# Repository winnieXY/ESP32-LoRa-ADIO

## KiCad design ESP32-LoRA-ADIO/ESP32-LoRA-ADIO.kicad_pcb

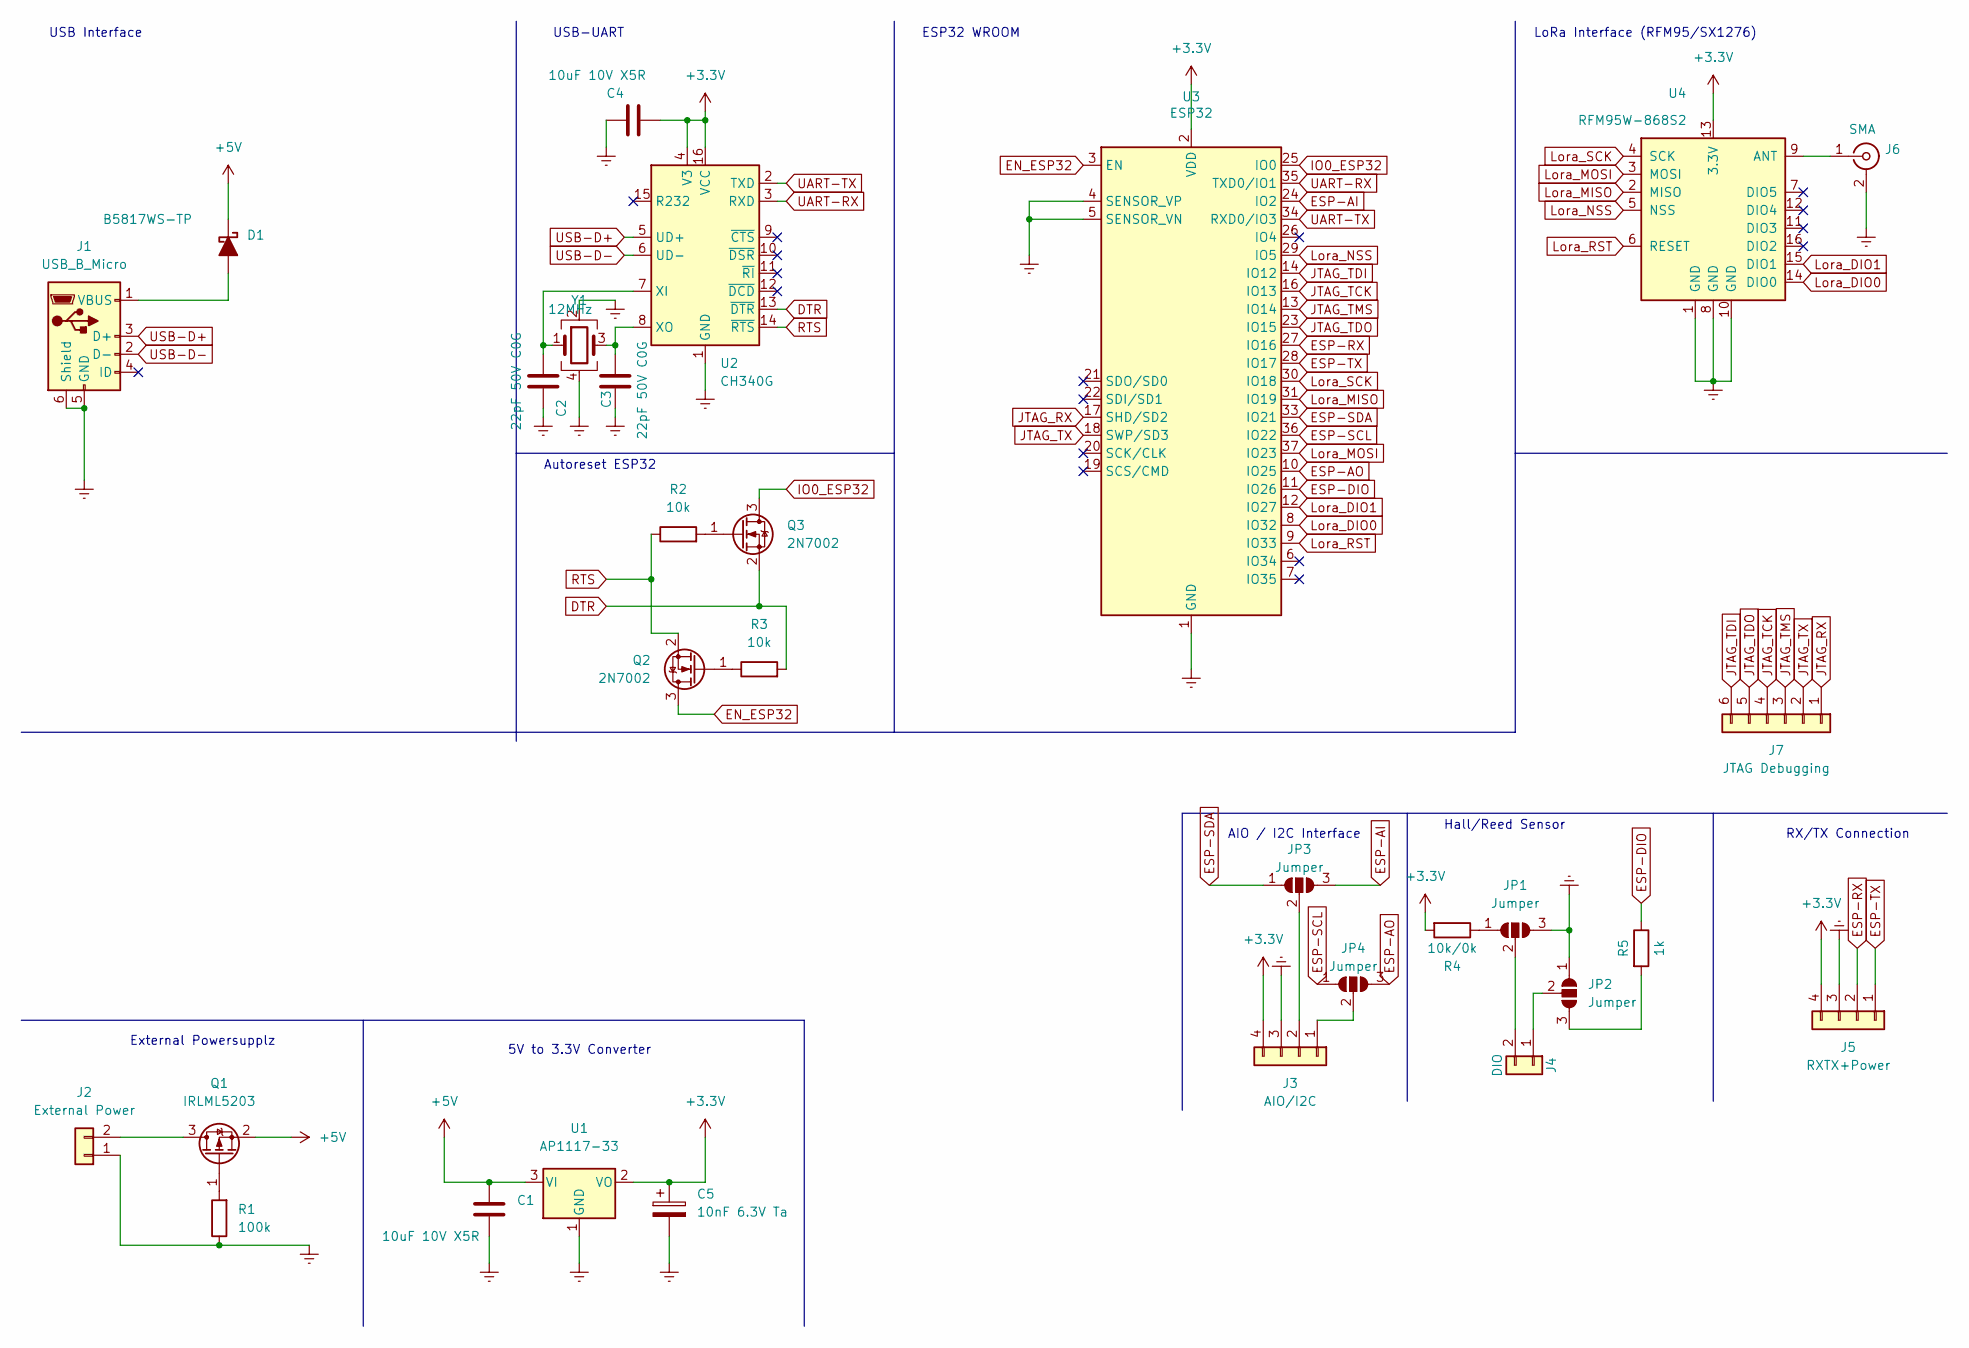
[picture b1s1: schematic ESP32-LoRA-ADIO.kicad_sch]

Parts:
C1, C4: 10uF 10V X5R; C_0603_1608Metric_Pad1.08x0.95mm_HandSolder; LCSC-Part C19702
C2, C3: 22pF 50V C0G; C_0603_1608Metric_Pad1.08x0.95mm_HandSolder; LCSC-Part C1653
C5: 10nF 6.3V Ta; CP_EIA-3528-15_AVX-H_Pad1.50x2.35mm_HandSolder; LCSC-Part C16133
D1: B5817WS-TP; D_SOD-323_HandSoldering; LCSC-Part C123899
J1: USB_B_Micro; GCT_USB3140-30-0230-1-C_REVE1
J2: External Power; JST_XH_B2B-XH-A_1x02_P2.50mm_Vertical
J3: AIO/I2C; JST_XH_B4B-XH-A_1x04_P2.50mm_Vertical
J4: DIO; JST_XH_B2B-XH-A_1x02_P2.50mm_Vertical
J5: RXTX+Power; JST_XH_B4B-XH-A_1x04_P2.50mm_Vertical
J6: SMA; SMA_Amphenol_901-144_Vertical
J7: JTAG Debugging; JST_XH_B6B-XH-A_1x06_P2.50mm_Vertical
JP1, JP2, JP3, JP4: Jumper; SolderJumper-3_P1.3mm_Open_Pad1.0x1.5mm
Q1: IRLML5203; SOT-23; LCSC-Part C2985623
Q2, Q3: 2N7002; SOT-23; LCSC-Part C350313
R1: 100k; R_1206_3216Metric_Pad1.30x1.75mm_HandSolder; LCSC-Part C269765
R2, R3: 10k; R_1206_3216Metric_Pad1.30x1.75mm_HandSolder; LCSC-Part C17902
R4: 10k/0k; R_1206_3216Metric_Pad1.30x1.75mm_HandSolder; LCSC-Part C136889 / C2907363
R5: 1k; R_1206_3216Metric_Pad1.30x1.75mm_HandSolder; LCSC-Part C4410
U1: AP1117-33; SOT-223-3_TabPin2; LCSC-Part C108785
U2: CH340G; SOIC-16_3.9x9.9mm_P1.27mm; LCSC-Part C14267
U3: ESP32; ESP32-WROOM-32; LCSC-Part C82899
U4: RFM95W-868S2; HOPERF_RFM9XW_SMD; LCSC-Part C2844473
Y1: 12MHz; Crystal_SMD_3225-4Pin_3.2x2.5mm_HandSoldering; LCSC-Part C9002

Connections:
+3V3: C4.2, C5.1, J3.4, J5.4, R4.2, U1.2 (VO), U2.4 (V3), U2.16 (VCC), U3.2 (VDD), U4.13 (3.3V)
+5V: C1.1, D1.1 (K), Q1.2 (S), U1.3 (VI)
DTR: Q3.2 (S), R3.2, U2.13 (~DTR)
EN_ESP32: Q2.3 (D), U3.3 (EN)
ESP-AI: JP3.3 (B), U3.24 (IO2)
ESP-AO: JP4.3 (B), U3.10 (IO25)
ESP-DIO: R5.1, U3.11 (IO26)
ESP-RX: J5.2, U3.27 (IO16)
ESP-SCL: JP4.1 (A), U3.36 (IO22)
ESP-SDA: JP3.1 (A), U3.33 (IO21)
ESP-TX: J5.1, U3.28 (IO17)
Earth: C1.2, C2.2, C3.2, C4.1, C5.2, J1.5 (GND), J1.6 (Shield), J2.1, J3.3, J5.3, J6.2 (Ext), JP1.3 (B), JP2.1 (A), R1.1, U1.1 (GND), U2.1 (GND), U3.1 (GND), U3.4 (SENSOR_VP), U3.5 (SENSOR_VN), U3.15 (GND), U3.38 (GND), U3.39 (GND), U4.1 (GND), U4.8 (GND), U4.10 (GND), Y1.2, Y1.4
IO0_ESP32: Q3.3 (D), U3.25 (IO0)
JTAG_RX: J7.1, U3.17 (SHD/SD2)
JTAG_TCK: J7.4, U3.16 (IO13)
JTAG_TDI: J7.6, U3.14 (IO12)
JTAG_TDO: J7.5, U3.23 (IO15)
JTAG_TMS: J7.3, U3.13 (IO14)
JTAG_TX: J7.2, U3.18 (SWP/SD3)
Lora_DIO0: U3.8 (IO32), U4.14 (DIO0)
Lora_DIO1: U3.12 (IO27), U4.15 (DIO1)
Lora_MISO: U3.31 (IO19), U4.2 (MISO)
Lora_MOSI: U3.37 (IO23), U4.3 (MOSI)
Lora_NSS: U3.29 (IO5), U4.5 (NSS)
Lora_RST: U3.9 (IO33), U4.6 (RESET)
Lora_SCK: U3.30 (IO18), U4.4 (SCK)
unnamed: C2.1, U2.7 (XI), Y1.1
unnamed: C3.1, U2.8 (XO), Y1.3
unnamed: D1.2 (A), J1.1 (VBUS)
unnamed: J2.2, Q1.3 (D)
unnamed: J3.1, JP4.2 (C)
unnamed: J3.2, JP3.2 (C)
unnamed: J4.1, JP2.2 (C)
unnamed: J4.2, JP1.2 (C)
unnamed: J6.1 (In), U4.9 (ANT)
unnamed: JP1.1 (A), R4.1
unnamed: JP2.3 (B), R5.2
unnamed: Q1.1 (G), R1.2
unnamed: Q2.1 (G), R3.1
unnamed: Q3.1 (G), R2.2
RTS: Q2.2 (S), R2.1, U2.14 (~RTS)
UART-RX: U2.3 (RXD), U3.35 (TXD0/IO1)
UART-TX: U2.2 (TXD), U3.34 (RXD0/IO3)
USB-D+: J1.3 (D+), U2.5 (UD+)
USB-D-: J1.2 (D-), U2.6 (UD-)

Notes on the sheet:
USB-UART
5V to 3.3V Converter
ESP32 WROOM
Autoreset ESP32
RX/TX Connection
USB Interface
AIO / I2C Interface
LoRa Interface (RFM95/SX1276)
External Powersupplz
Hall/Reed Sensor

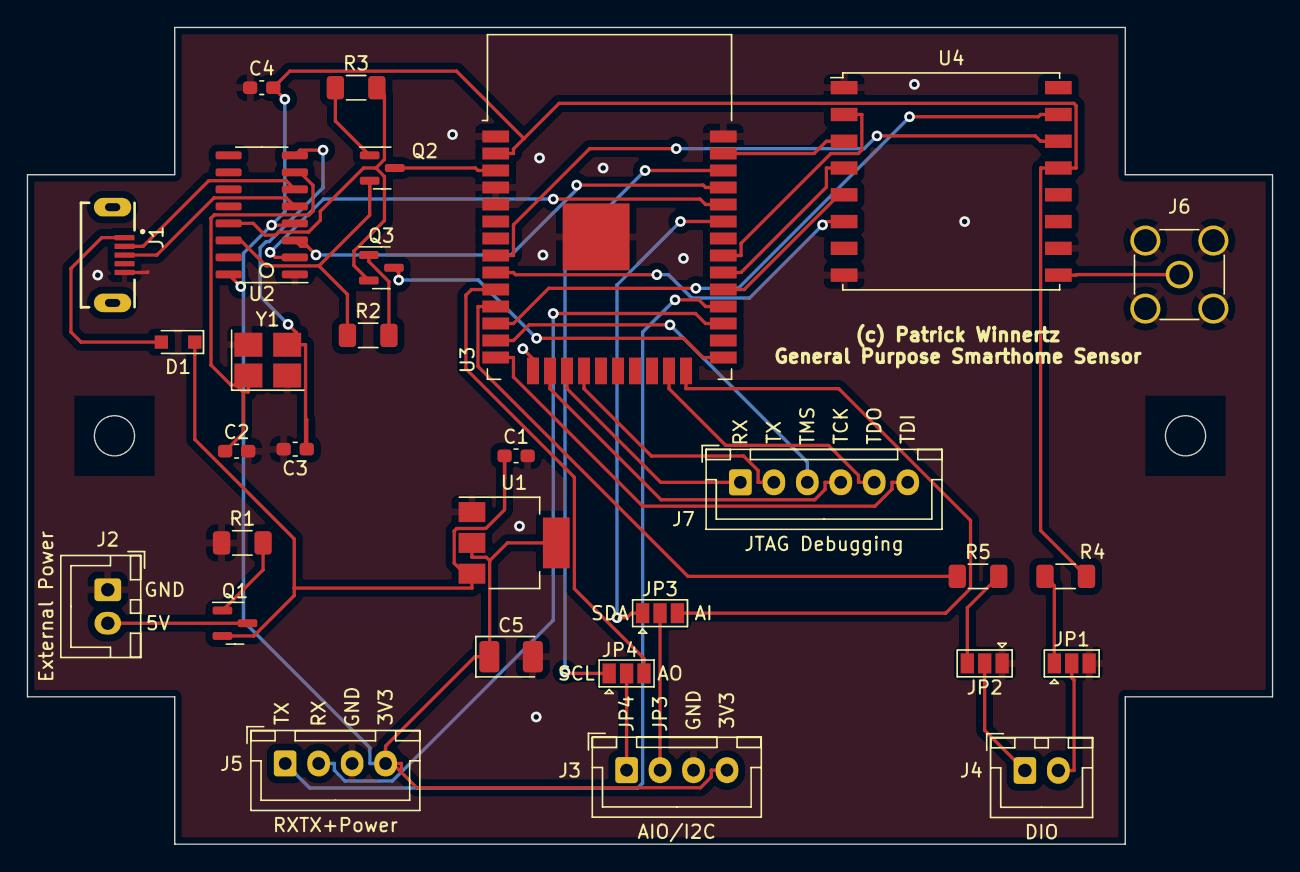
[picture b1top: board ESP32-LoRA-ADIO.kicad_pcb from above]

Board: 2 copper layers, 93.0 x 61.0 mm, 30 parts (0 on the bottom side), 45 nets.

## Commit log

2022-07-04 Rotated the schottky diode for the next Revision
2022-07-04 Change PCB layout a bit to fit better into the case
2022-07-04 Some more refinements to the PCB board
2022-07-04 Ignore backup files - we have now the git
2022-07-04 Remove the zips from the git
2022-07-11 Add JTAG debug interface to schematics
2022-09-02 Add a AI and add jumpers to the AI/I2C slot
2022-09-05 Started to separate SPI and JTAG to be able to use both at the same time
2022-09-05 Finalized the labeling - now the PCB needs to be changed
2022-09-05 Autorouting the new spi wiring
2022-09-06 Added labels and get rid of some warnings
2022-09-06 Some minor modifications to the schema
2022-09-12 Replaced the Micro USB connector by a vertical one
2022-09-12 Use relative paths to the symbol files in order to make it work on several computers
